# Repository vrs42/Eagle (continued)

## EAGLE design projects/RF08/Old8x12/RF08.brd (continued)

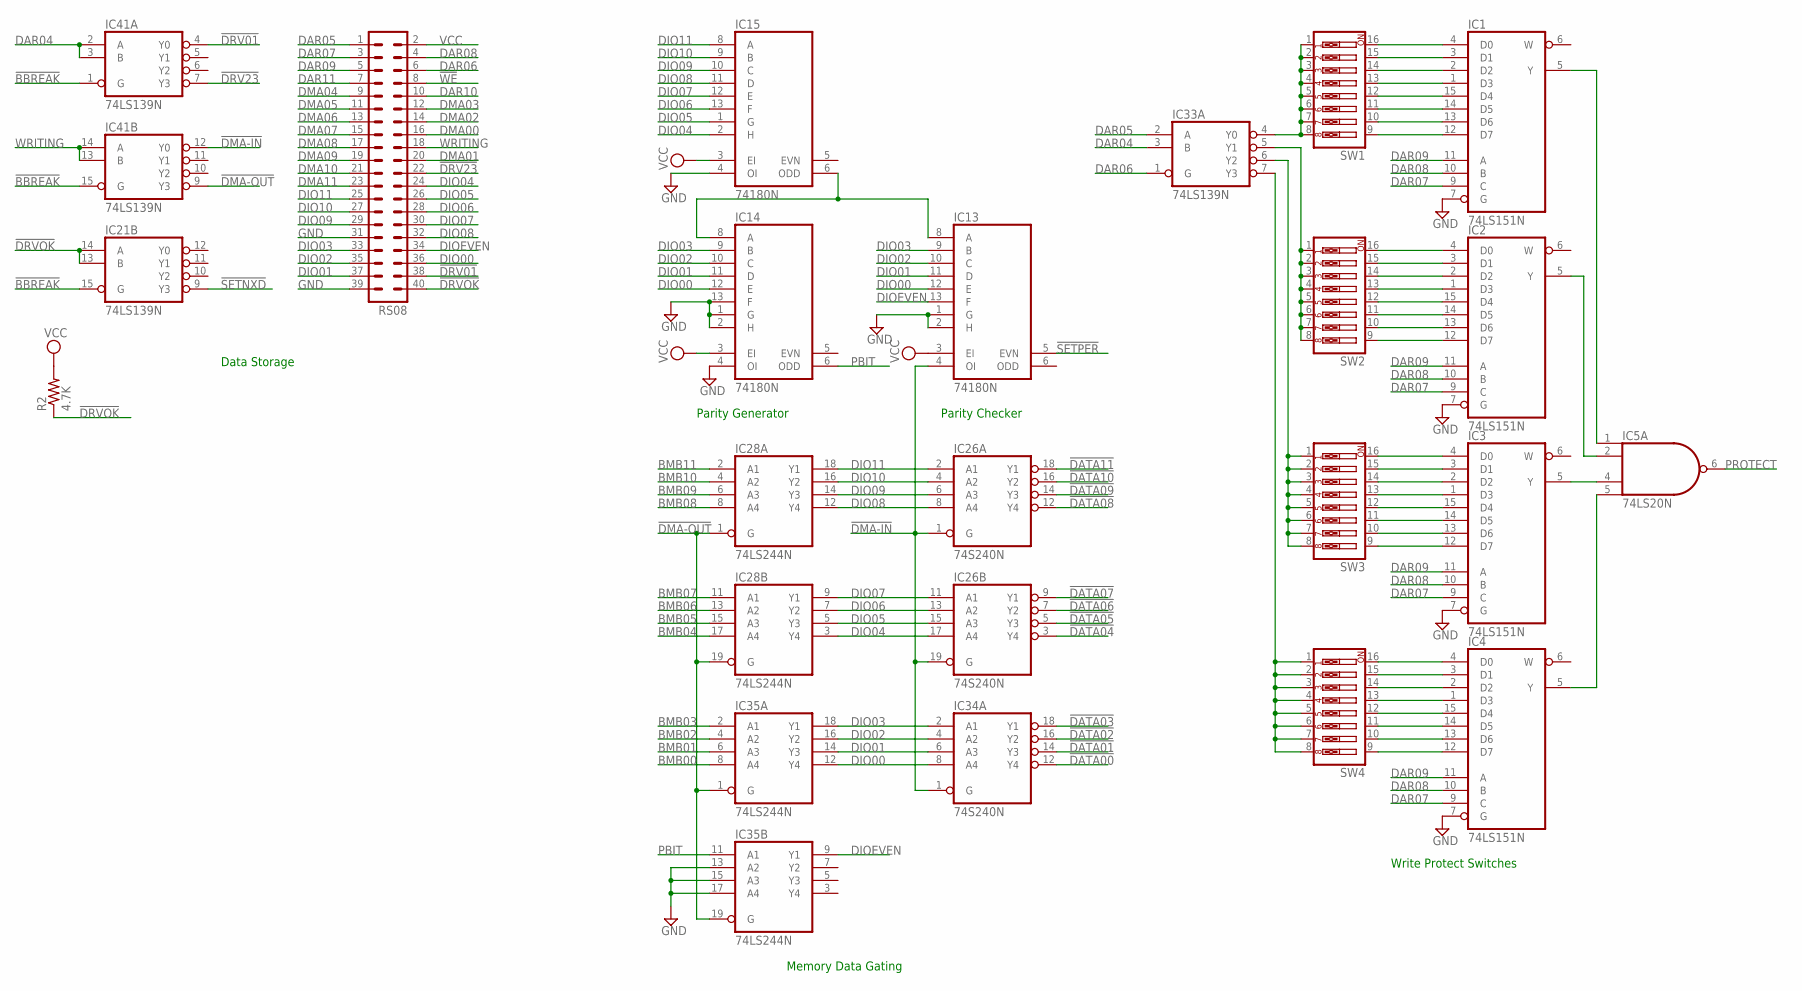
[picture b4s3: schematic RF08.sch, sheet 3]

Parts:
IC1, IC2, IC3, IC4: 74LS151N; DIL16
IC5: 74LS20N; DIL14
IC13, IC14, IC15: 74180N; DIL14
IC21, IC33, IC41: 74LS139N; DIL16
IC26, IC34: 74S240N; DIL20
IC28, IC35: 74LS244N; DIL20
R2: 4.7K; 0207/10
RS08: MA20-2
SW1, SW2, SW3, SW4: SW_DIP-8; EDG-08

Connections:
!BBREAK: IC21.15 (G), IC41.1 (G), IC41.15 (G); also elsewhere on the board
!DATA00: IC34.12 (Y4); also elsewhere on the board
!DATA01: IC34.14 (Y3); also elsewhere on the board
!DATA02: IC34.16 (Y2); also elsewhere on the board
!DATA03: IC34.18 (Y1); also elsewhere on the board
!DATA04: IC26.3 (Y4); also elsewhere on the board
!DATA05: IC26.5 (Y3); also elsewhere on the board
!DATA06: IC26.7 (Y2); also elsewhere on the board
!DATA07: IC26.9 (Y1); also elsewhere on the board
!DATA08: IC26.12 (Y4); also elsewhere on the board
!DATA09: IC26.14 (Y3); also elsewhere on the board
!DATA10: IC26.16 (Y2); also elsewhere on the board
!DATA11: IC26.18 (Y1); also elsewhere on the board
!DMA-IN: IC13.4 (OI), IC26.1 (G), IC26.19 (G), IC34.1 (G), IC41.12 (Y0)
!DMA-OUT: IC28.1 (G), IC28.19 (G), IC35.1 (G), IC35.19 (G), IC41.9 (Y3)
!DRV01: IC41.4 (Y0), RS08.38
!DRV23: IC41.7 (Y3), RS08.22
!DRVOK: IC21.13 (B), IC21.14 (A), R2.1, RS08.40
!SETNXD: IC21.9 (Y3); also elsewhere on the board
!SETPER: IC13.5 (EVN); also elsewhere on the board
!WE: RS08.8; also elsewhere on the board
BMB00: IC35.8 (A4); also elsewhere on the board
BMB01: IC35.6 (A3); also elsewhere on the board
BMB02: IC35.4 (A2); also elsewhere on the board
BMB03: IC35.2 (A1); also elsewhere on the board
BMB04: IC28.17 (A4); also elsewhere on the board
BMB05: IC28.15 (A3); also elsewhere on the board
BMB06: IC28.13 (A2); also elsewhere on the board
BMB07: IC28.11 (A1); also elsewhere on the board
BMB08: IC28.8 (A4); also elsewhere on the board
BMB09: IC28.6 (A3); also elsewhere on the board
BMB10: IC28.4 (A2); also elsewhere on the board
BMB11: IC28.2 (A1); also elsewhere on the board
DAR04: IC33.3 (B), IC41.2 (A), IC41.3 (B); also elsewhere on the board
DAR05: IC33.2 (A), RS08.1; also elsewhere on the board
DAR06: IC33.1 (G), RS08.6; also elsewhere on the board
DAR07: IC1.9 (C), IC2.9 (C), IC3.9 (C), IC4.9 (C), RS08.3; also elsewhere on the board
DAR08: IC1.10 (B), IC2.10 (B), IC3.10 (B), IC4.10 (B), RS08.4; also elsewhere on the board
DAR09: IC1.11 (A), IC2.11 (A), IC3.11 (A), IC4.11 (A), RS08.5; also elsewhere on the board
DAR10: RS08.10; also elsewhere on the board
DAR11: RS08.7; also elsewhere on the board
DIO00: IC13.12 (E), IC14.12 (E), IC34.8 (A4), IC35.12 (Y4), RS08.36
DIO01: IC13.11 (D), IC14.11 (D), IC34.6 (A3), IC35.14 (Y3), RS08.37
DIO02: IC13.10 (C), IC14.10 (C), IC34.4 (A2), IC35.16 (Y2), RS08.35
DIO03: IC13.9 (B), IC14.9 (B), IC34.2 (A1), IC35.18 (Y1), RS08.33
DIO04: IC15.2 (H), IC26.17 (A4), IC28.3 (Y4), RS08.24
DIO05: IC15.1 (G), IC26.15 (A3), IC28.5 (Y3), RS08.26
DIO06: IC15.13 (F), IC26.13 (A2), IC28.7 (Y2), RS08.28
DIO07: IC15.12 (E), IC26.11 (A1), IC28.9 (Y1), RS08.30
DIO08: IC15.11 (D), IC26.8 (A4), IC28.12 (Y4), RS08.32
DIO09: IC15.10 (C), IC26.6 (A3), IC28.14 (Y3), RS08.29
DIO10: IC15.9 (B), IC26.4 (A2), IC28.16 (Y2), RS08.27
DIO11: IC15.8 (A), IC26.2 (A1), IC28.18 (Y1), RS08.25
DIOEVEN: IC13.13 (F), IC35.9 (Y1), RS08.34
DMA00: RS08.16; also elsewhere on the board
DMA01: RS08.20; also elsewhere on the board
DMA02: RS08.14; also elsewhere on the board
DMA03: RS08.12; also elsewhere on the board
DMA04: RS08.9; also elsewhere on the board
DMA05: RS08.11; also elsewhere on the board
DMA06: RS08.13; also elsewhere on the board
DMA07: RS08.15; also elsewhere on the board
DMA08: RS08.17; also elsewhere on the board
DMA09: RS08.19; also elsewhere on the board
DMA10: RS08.21; also elsewhere on the board
DMA11: RS08.23; also elsewhere on the board
GND: IC1.7 (G), IC1.8 (GND), IC2.7 (G), IC2.8 (GND), IC3.7 (G), IC3.8 (GND), IC4.7 (G), IC4.8 (GND), IC5.7 (GND), IC13.1 (G), IC13.2 (H), IC13.7 (GND), IC14.1 (G), IC14.2 (H), IC14.4 (OI), IC14.7 (GND), IC14.13 (F), IC15.4 (OI), IC15.7 (GND), IC21.8 (GND), IC26.10 (GND), IC28.10 (GND), IC33.8 (GND), IC34.10 (GND), IC35.10 (GND), IC35.13 (A2), IC35.15 (A3), IC35.17 (A4), IC41.8 (GND), RS08.31, RS08.39; also elsewhere on the board
unnamed: IC33.4 (Y0), SW1.1, SW1.2, SW1.3, SW1.4, SW1.5, SW1.6, SW1.7, SW1.8
unnamed: IC13.8 (A), IC14.8 (A), IC15.6 (ODD)
unnamed: IC2.5 (Y), IC5.2 (I1)
unnamed: IC33.5 (Y1), SW2.1, SW2.2, SW2.3, SW2.4, SW2.5, SW2.6, SW2.7, SW2.8
unnamed: IC33.6 (Y2), SW3.1, SW3.2, SW3.3, SW3.4, SW3.5, SW3.6, SW3.7, SW3.8
unnamed: IC33.7 (Y3), SW4.1, SW4.2, SW4.3, SW4.4, SW4.5, SW4.6, SW4.7, SW4.8
unnamed: IC3.5 (Y), IC5.4 (I2)
unnamed: IC1.5 (Y), IC5.1 (I0)
unnamed: IC4.5 (Y), IC5.5 (I3)
unnamed: IC1.4 (D0), SW1.16
unnamed: IC1.3 (D1), SW1.15
unnamed: IC1.2 (D2), SW1.14
unnamed: IC1.1 (D3), SW1.13
unnamed: IC1.14 (D5), SW1.11
unnamed: IC1.13 (D6), SW1.10
unnamed: IC1.12 (D7), SW1.9
unnamed: IC1.15 (D4), SW1.12
unnamed: IC2.4 (D0), SW2.16
unnamed: IC2.3 (D1), SW2.15
unnamed: IC2.2 (D2), SW2.14
unnamed: IC2.1 (D3), SW2.13
unnamed: IC2.14 (D5), SW2.11
unnamed: IC2.13 (D6), SW2.10
unnamed: IC2.12 (D7), SW2.9
unnamed: IC3.4 (D0), SW3.16
unnamed: IC3.3 (D1), SW3.15
unnamed: IC3.2 (D2), SW3.14
unnamed: IC3.1 (D3), SW3.13
unnamed: IC3.14 (D5), SW3.11
unnamed: IC3.13 (D6), SW3.10
unnamed: IC3.12 (D7), SW3.9
unnamed: IC4.4 (D0), SW4.16
unnamed: IC4.3 (D1), SW4.15
unnamed: IC4.2 (D2), SW4.14
unnamed: IC4.1 (D3), SW4.13
unnamed: IC4.14 (D5), SW4.11
unnamed: IC4.13 (D6), SW4.10
unnamed: IC4.12 (D7), SW4.9
unnamed: IC4.15 (D4), SW4.12
unnamed: IC3.15 (D4), SW3.12
unnamed: IC2.15 (D4), SW2.12
PBIT: IC14.6 (ODD), IC35.11 (A1)
PROTECT: IC5.6 (O); also elsewhere on the board
VCC: IC1.16 (VCC), IC2.16 (VCC), IC3.16 (VCC), IC4.16 (VCC), IC5.14 (VCC), IC13.3 (EI), IC13.14 (VCC), IC14.3 (EI), IC14.14 (VCC), IC15.3 (EI), IC15.14 (VCC), IC21.16 (VCC), IC26.20 (VCC), IC28.20 (VCC), IC33.16 (VCC), IC34.20 (VCC), IC35.20 (VCC), IC41.16 (VCC), R2.2, RS08.2; also elsewhere on the board
WRITING: IC41.13 (B), IC41.14 (A), RS08.18; also elsewhere on the board

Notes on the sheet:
Parity Generator
Parity Checker
Memory Data Gating
Write Protect Switches
Data Storage

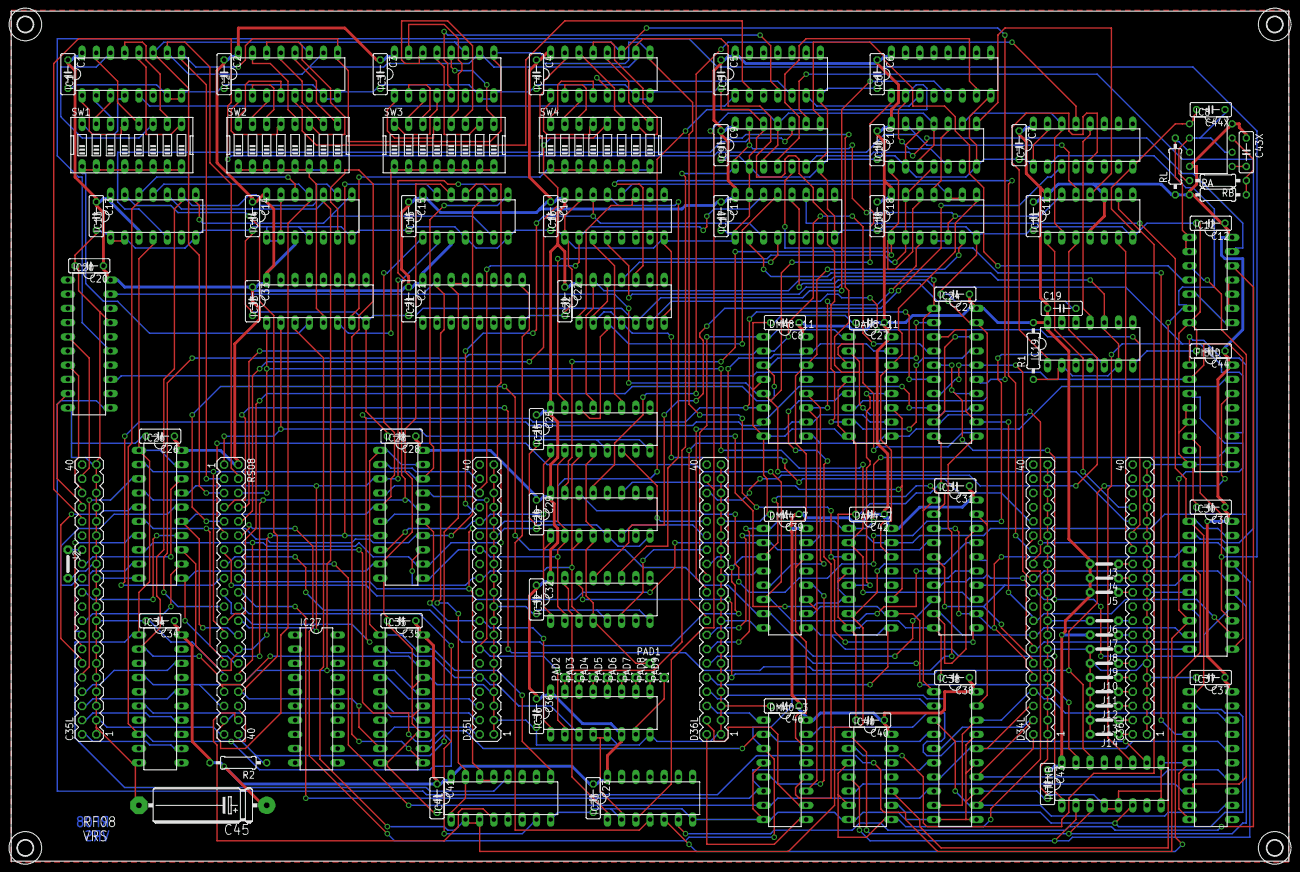
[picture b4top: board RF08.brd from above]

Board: 2 copper layers, 228.6 x 152.1 mm, 136 parts (0 on the bottom side), 226 nets.

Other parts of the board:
U$1, U$2, U$3, U$4: 2,8

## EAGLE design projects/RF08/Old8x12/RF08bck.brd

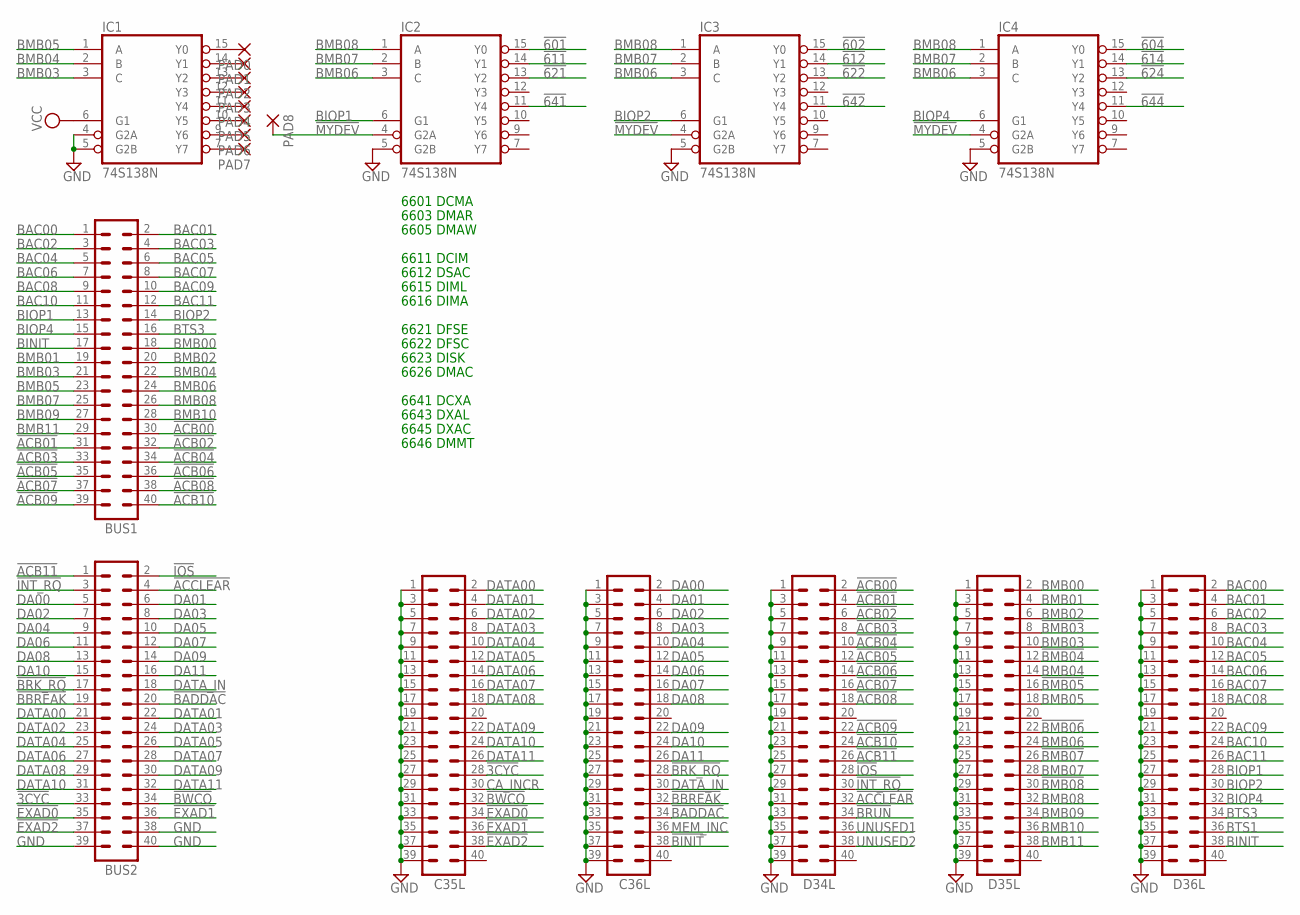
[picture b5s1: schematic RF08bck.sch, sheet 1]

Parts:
BUS1, BUS2: MA20-2
C35L, C36L: MA20-2
D34L, D35L, D36L: MA20-2
IC1, IC2, IC3, IC4: 74S138N; DIL16
PAD0, PAD1, PAD2, PAD3, PAD4, PAD5, PAD6, PAD7, PAD8: 1,6/0,8

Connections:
!3CYC: BUS2.33, C35L.28
!601: IC2.15 (Y0); also elsewhere on the board
!602: IC3.15 (Y0); also elsewhere on the board
!604: IC4.15 (Y0); also elsewhere on the board
!611: IC2.14 (Y1)
!612: IC3.14 (Y1)
!614: IC4.14 (Y1)
!621: IC2.13 (Y2)
!622: IC3.13 (Y2)
!624: IC4.13 (Y2); also elsewhere on the board
!641: IC2.11 (Y4)
!642: IC3.11 (Y4)
!644: IC4.11 (Y4)
!ACB00: BUS1.30, D34L.2; also elsewhere on the board
!ACB01: BUS1.31, D34L.4; also elsewhere on the board
!ACB02: BUS1.32, D34L.6; also elsewhere on the board
!ACB03: BUS1.33, D34L.8; also elsewhere on the board
!ACB04: BUS1.34, D34L.10; also elsewhere on the board
!ACB05: BUS1.35, D34L.12; also elsewhere on the board
!ACB06: BUS1.36, D34L.14; also elsewhere on the board
!ACB07: BUS1.37, D34L.16; also elsewhere on the board
!ACB08: BUS1.38, D34L.18; also elsewhere on the board
!ACB09: BUS1.39, D34L.22; also elsewhere on the board
!ACB10: BUS1.40, D34L.24; also elsewhere on the board
!ACB11: BUS2.1, D34L.26; also elsewhere on the board
!ACCLEAR: BUS2.4, D34L.32
!BADDAC: BUS2.20, C36L.34
!BBREAK: BUS2.19, C36L.32
!BINIT: C36L.38
!BMB03: D35L.8
!BMB04: D35L.12
!BMB05: D35L.16
!BMB06: D35L.22
!BMB07: D35L.26
!BMB08: D35L.30
!BRK_RQ: BUS2.17, C36L.28
!BRUN: D34L.34
!BWCO: BUS2.34, C35L.32
!EXAD0: BUS2.35, C35L.34
!EXAD1: BUS2.36, C35L.36
!EXAD2: BUS2.37, C35L.38
!INT_RQ: BUS2.3, D34L.30
!IOS: BUS2.2, D34L.28
!MYDEV: IC2.4 (G2A), IC3.4 (G2A), IC4.4 (G2A), PAD8.1
BAC00: BUS1.1, D36L.2; also elsewhere on the board
BAC01: BUS1.2, D36L.4; also elsewhere on the board
BAC02: BUS1.3, D36L.6; also elsewhere on the board
BAC03: BUS1.4, D36L.8; also elsewhere on the board
BAC04: BUS1.5, D36L.10; also elsewhere on the board
BAC05: BUS1.6, D36L.12; also elsewhere on the board
BAC06: BUS1.7, D36L.14; also elsewhere on the board
BAC07: BUS1.8, D36L.16; also elsewhere on the board
BAC08: BUS1.9, D36L.18; also elsewhere on the board
BAC09: BUS1.10, D36L.22; also elsewhere on the board
BAC10: BUS1.11, D36L.24; also elsewhere on the board
BAC11: BUS1.12, D36L.26; also elsewhere on the board
BINIT: BUS1.17, D36L.38
BIOP1: BUS1.13, D36L.28, IC2.6 (G1)
BIOP2: BUS1.14, D36L.30, IC3.6 (G1)
BIOP4: BUS1.15, D36L.32, IC4.6 (G1)
BMB00: BUS1.18, D35L.2
BMB01: BUS1.19, D35L.4
BMB02: BUS1.20, D35L.6
BMB03: BUS1.21, D35L.10, IC1.3 (C)
BMB04: BUS1.22, D35L.14, IC1.2 (B)
BMB05: BUS1.23, D35L.18, IC1.1 (A)
BMB06: BUS1.24, D35L.24, IC2.3 (C), IC3.3 (C), IC4.3 (C)
BMB07: BUS1.25, D35L.28, IC2.2 (B), IC3.2 (B), IC4.2 (B)
BMB08: BUS1.26, D35L.32, IC2.1 (A), IC3.1 (A), IC4.1 (A)
BMB09: BUS1.27, D35L.34
BMB10: BUS1.28, D35L.36
BMB11: BUS1.29, D35L.38
BTS1: D36L.36
BTS3: BUS1.16, D36L.34
CA_INCR: C35L.30
DA00: BUS2.5, C36L.2
DA01: BUS2.6, C36L.4
DA02: BUS2.7, C36L.6
DA03: BUS2.8, C36L.8
DA04: BUS2.9, C36L.10
DA05: BUS2.10, C36L.12
DA06: BUS2.11, C36L.14
DA07: BUS2.12, C36L.16
DA08: BUS2.13, C36L.18
DA09: BUS2.14, C36L.22
DA10: BUS2.15, C36L.24
DA11: BUS2.16, C36L.26
DATA00: BUS2.21, C35L.2
DATA01: BUS2.22, C35L.4
DATA02: BUS2.23, C35L.6
DATA03: BUS2.24, C35L.8
DATA04: BUS2.25, C35L.10
DATA05: BUS2.26, C35L.12
DATA06: BUS2.27, C35L.14
DATA07: BUS2.28, C35L.16
DATA08: BUS2.29, C35L.18
DATA09: BUS2.30, C35L.22
DATA10: BUS2.31, C35L.24
DATA11: BUS2.32, C35L.26
DATA_IN: BUS2.18, C36L.30
GND: BUS2.38, BUS2.39, BUS2.40, C35L.1, C35L.3, C35L.5, C35L.7, C35L.9, C35L.11, C35L.13, C35L.15, C35L.17, C35L.19, C35L.21, C35L.23, C35L.25, C35L.27, C35L.29, C35L.31, C35L.33, C35L.35, C35L.37, C35L.39, C36L.1, C36L.3, C36L.5, C36L.7, C36L.9, C36L.11, C36L.13, C36L.15, C36L.17, C36L.19, C36L.21, C36L.23, C36L.25, C36L.27, C36L.29, C36L.31, C36L.33, C36L.35, C36L.37, C36L.39, D34L.1, D34L.3, D34L.5, D34L.7, D34L.9, D34L.11, D34L.13, D34L.15, D34L.17, D34L.19, D34L.21, D34L.23, D34L.25, D34L.27, D34L.29, D34L.31, D34L.33, D34L.35, D34L.37, D34L.39, D35L.1, D35L.3, D35L.5, D35L.7, D35L.9, D35L.11, D35L.13, D35L.15, D35L.17, D35L.19, D35L.21, D35L.23, D35L.25, D35L.27, D35L.29, D35L.31, D35L.33, D35L.35, D35L.37, D35L.39, D36L.1, D36L.3, D36L.5, D36L.7, D36L.9, D36L.11, D36L.13, D36L.15, D36L.17, D36L.19, D36L.21, D36L.23, D36L.25, D36L.27, D36L.29, D36L.31, D36L.33, D36L.35, D36L.37, D36L.39, IC1.4 (G2A), IC1.5 (G2B), IC1.8 (GND), IC2.5 (G2B), IC2.8 (GND), IC3.5 (G2B), IC3.8 (GND), IC4.5 (G2B), IC4.8 (GND); also elsewhere on the board
MEM_INC: C36L.36
unnamed: IC1.9 (Y6), PAD6.1
unnamed: IC1.15 (Y0), PAD0.1
unnamed: IC1.14 (Y1), PAD1.1
unnamed: IC1.13 (Y2), PAD2.1
unnamed: IC1.12 (Y3), PAD3.1
unnamed: IC1.11 (Y4), PAD4.1
unnamed: IC1.10 (Y5), PAD5.1
unnamed: IC1.7 (Y7), PAD7.1
UNUSED1: D34L.36
UNUSED2: D34L.38
VCC: IC1.6 (G1), IC1.16 (VCC), IC2.16 (VCC), IC3.16 (VCC), IC4.16 (VCC); also elsewhere on the board

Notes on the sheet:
6601 DCMA
6603 DMAR
6605 DMAW
6611 DCIM
6612 DSAC
6615 DIML
6616 DIMA
6621 DFSE
6622 DFSC
6623 DISK
6626 DMAC
6641 DCXA
6643 DXAL
6645 DXAC
6646 DMMT

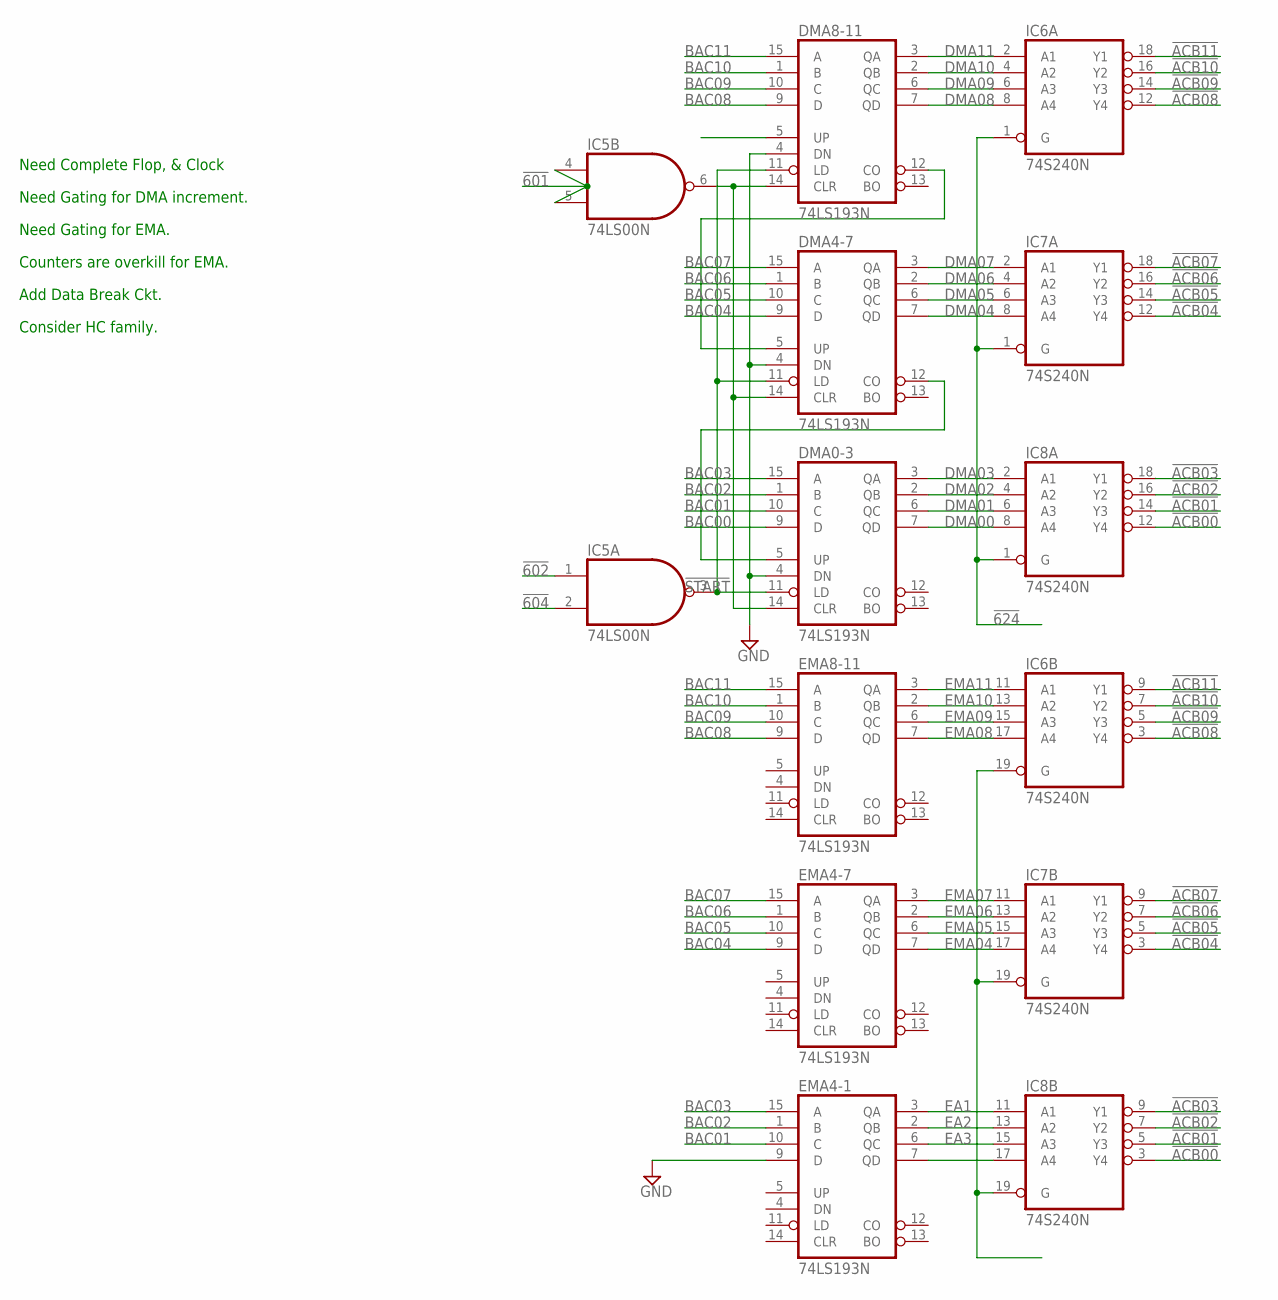
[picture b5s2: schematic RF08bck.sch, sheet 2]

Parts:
DMA0-3, DMA4-7, DMA8-11: 74LS193N; DIL16
EMA4-1, EMA4-7, EMA8-11: 74LS193N; DIL16
IC5: 74LS00N; DIL14
IC6, IC7, IC8: 74S240N; DIL20

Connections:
!601: IC5.4 (I0), IC5.5 (I1); also elsewhere on the board
!602: IC5.1 (I0); also elsewhere on the board
!604: IC5.2 (I1); also elsewhere on the board
!624: IC6.1 (G), IC7.1 (G), IC8.1 (G); also elsewhere on the board
!ACB00: IC8.3 (Y4), IC8.12 (Y4); also elsewhere on the board
!ACB01: IC8.5 (Y3), IC8.14 (Y3); also elsewhere on the board
!ACB02: IC8.7 (Y2), IC8.16 (Y2); also elsewhere on the board
!ACB03: IC8.9 (Y1), IC8.18 (Y1); also elsewhere on the board
!ACB04: IC7.3 (Y4), IC7.12 (Y4); also elsewhere on the board
!ACB05: IC7.5 (Y3), IC7.14 (Y3); also elsewhere on the board
!ACB06: IC7.7 (Y2), IC7.16 (Y2); also elsewhere on the board
!ACB07: IC7.9 (Y1), IC7.18 (Y1); also elsewhere on the board
!ACB08: IC6.3 (Y4), IC6.12 (Y4); also elsewhere on the board
!ACB09: IC6.5 (Y3), IC6.14 (Y3); also elsewhere on the board
!ACB10: IC6.7 (Y2), IC6.16 (Y2); also elsewhere on the board
!ACB11: IC6.9 (Y1), IC6.18 (Y1); also elsewhere on the board
!START: DMA0-3.11 (LD), DMA4-7.11 (LD), DMA8-11.11 (LD), IC5.3 (O)
BAC00: DMA0-3.9 (D); also elsewhere on the board
BAC01: DMA0-3.10 (C), EMA4-1.10 (C); also elsewhere on the board
BAC02: DMA0-3.1 (B), EMA4-1.1 (B); also elsewhere on the board
BAC03: DMA0-3.15 (A), EMA4-1.15 (A); also elsewhere on the board
BAC04: DMA4-7.9 (D), EMA4-7.9 (D); also elsewhere on the board
BAC05: DMA4-7.10 (C), EMA4-7.10 (C); also elsewhere on the board
BAC06: DMA4-7.1 (B), EMA4-7.1 (B); also elsewhere on the board
BAC07: DMA4-7.15 (A), EMA4-7.15 (A); also elsewhere on the board
BAC08: DMA8-11.9 (D), EMA8-11.9 (D); also elsewhere on the board
BAC09: DMA8-11.10 (C), EMA8-11.10 (C); also elsewhere on the board
BAC10: DMA8-11.1 (B), EMA8-11.1 (B); also elsewhere on the board
BAC11: DMA8-11.15 (A), EMA8-11.15 (A); also elsewhere on the board
DMA00: DMA0-3.7 (QD), IC8.8 (A4)
DMA01: DMA0-3.6 (QC), IC8.6 (A3)
DMA02: DMA0-3.2 (QB), IC8.4 (A2)
DMA03: DMA0-3.3 (QA), IC8.2 (A1)
DMA04: DMA4-7.7 (QD), IC7.8 (A4)
DMA05: DMA4-7.6 (QC), IC7.6 (A3)
DMA06: DMA4-7.2 (QB), IC7.4 (A2)
DMA07: DMA4-7.3 (QA), IC7.2 (A1)
DMA08: DMA8-11.7 (QD), IC6.8 (A4)
DMA09: DMA8-11.6 (QC), IC6.6 (A3)
DMA10: DMA8-11.2 (QB), IC6.4 (A2)
DMA11: DMA8-11.3 (QA), IC6.2 (A1)
EA1: EMA4-1.3 (QA), IC8.11 (A1)
EA2: EMA4-1.2 (QB), IC8.13 (A2)
EA3: EMA4-1.6 (QC), IC8.15 (A3)
EMA04: EMA4-7.7 (QD), IC7.17 (A4)
EMA05: EMA4-7.6 (QC), IC7.15 (A3)
EMA06: EMA4-7.2 (QB), IC7.13 (A2)
EMA07: EMA4-7.3 (QA), IC7.11 (A1)
EMA08: EMA8-11.7 (QD), IC6.17 (A4)
EMA09: EMA8-11.6 (QC), IC6.15 (A3)
EMA10: EMA8-11.2 (QB), IC6.13 (A2)
EMA11: EMA8-11.3 (QA), IC6.11 (A1)
GND: DMA0-3.4 (DN), DMA0-3.8 (GND), DMA4-7.4 (DN), DMA4-7.8 (GND), DMA8-11.4 (DN), DMA8-11.8 (GND), EMA4-1.8 (GND), EMA4-1.9 (D), EMA4-7.8 (GND), EMA8-11.8 (GND), IC5.7 (GND), IC6.10 (GND), IC7.10 (GND), IC8.10 (GND); also elsewhere on the board
unnamed: DMA0-3.5 (UP), DMA4-7.12 (CO)
unnamed: EMA4-1.7 (QD), IC8.17 (A4)
unnamed: DMA4-7.5 (UP), DMA8-11.12 (CO)
unnamed: IC6.19 (G), IC7.19 (G), IC8.19 (G)
unnamed: DMA0-3.14 (CLR), DMA4-7.14 (CLR), DMA8-11.14 (CLR), IC5.6 (O)
VCC: DMA0-3.16 (VCC), DMA4-7.16 (VCC), DMA8-11.16 (VCC), EMA4-1.16 (VCC), EMA4-7.16 (VCC), EMA8-11.16 (VCC), IC5.14 (VCC), IC6.20 (VCC), IC7.20 (VCC), IC8.20 (VCC); also elsewhere on the board

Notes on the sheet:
Need Complete Flop, & Clock
Need Gating for DMA increment.
Need Gating for EMA.
Counters are overkill for EMA.
Add Data Break Ckt.
Consider HC family.

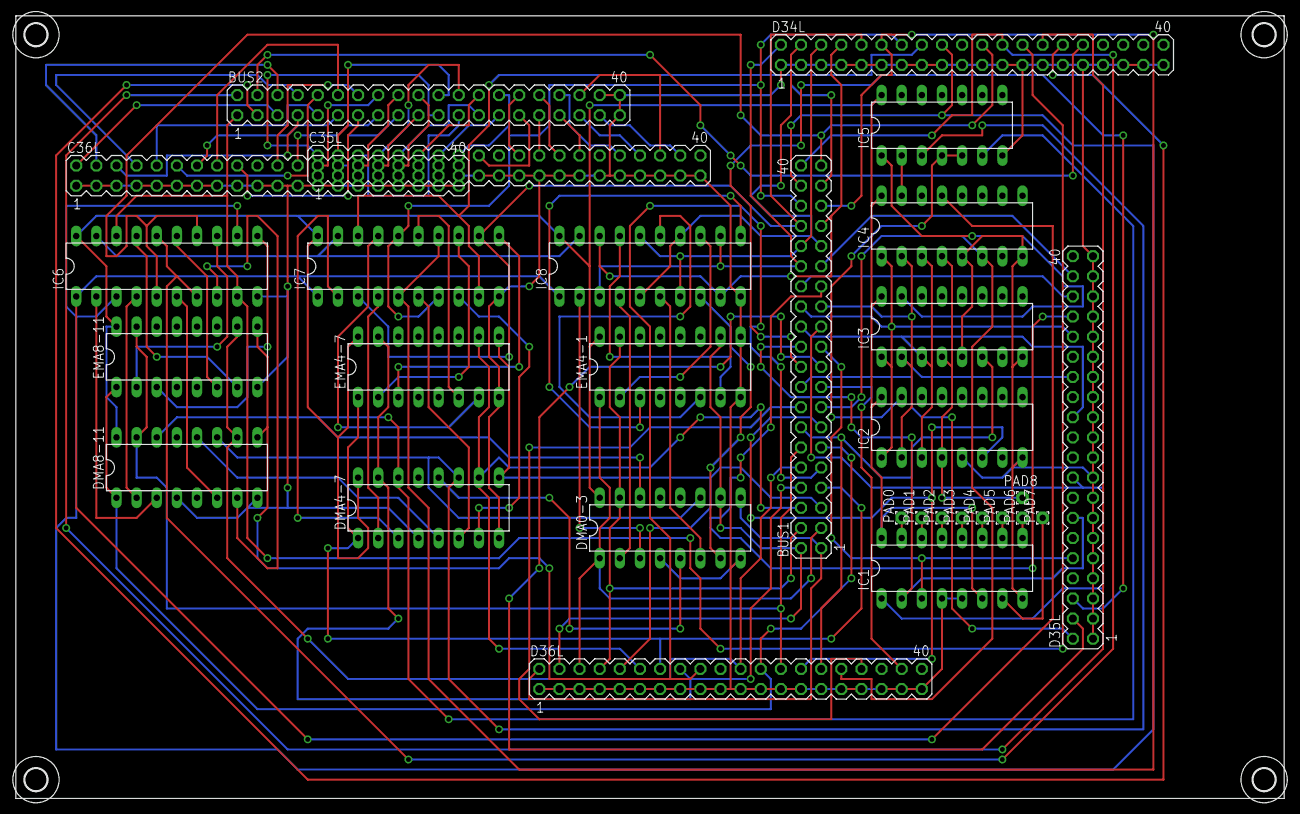
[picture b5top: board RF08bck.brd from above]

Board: 2 copper layers, 160.0 x 98.7 mm, 34 parts (0 on the bottom side), 121 nets.

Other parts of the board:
U$1, U$2, U$3, U$4: 2,8
